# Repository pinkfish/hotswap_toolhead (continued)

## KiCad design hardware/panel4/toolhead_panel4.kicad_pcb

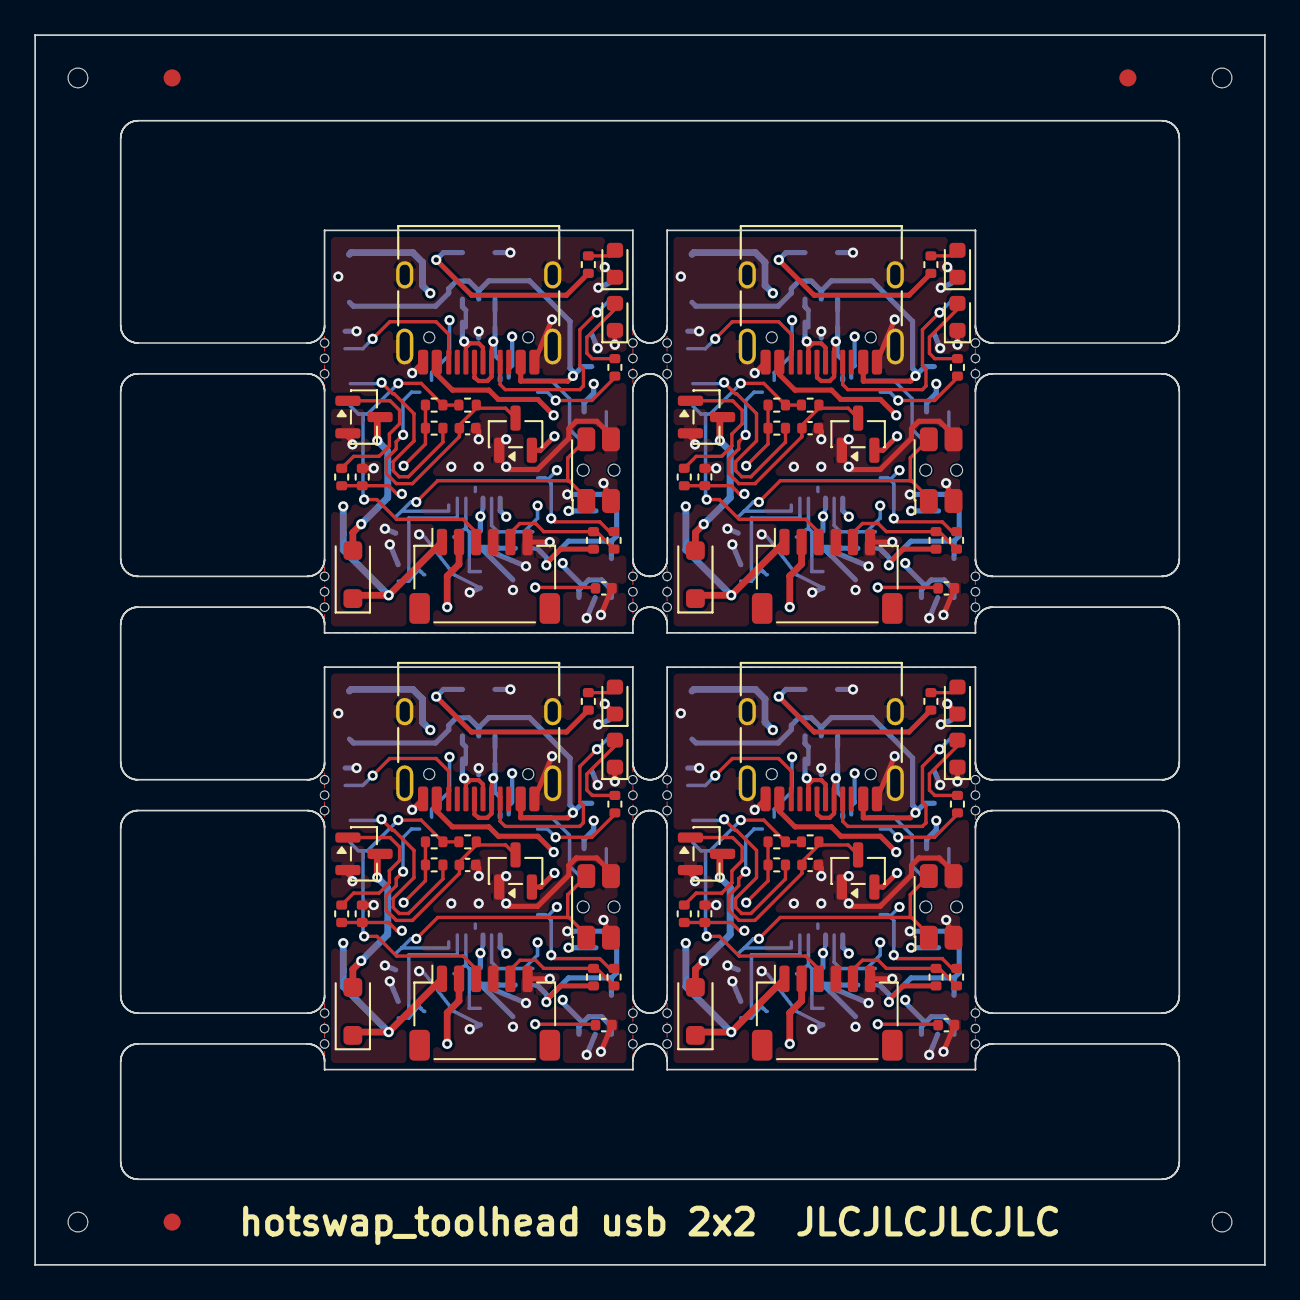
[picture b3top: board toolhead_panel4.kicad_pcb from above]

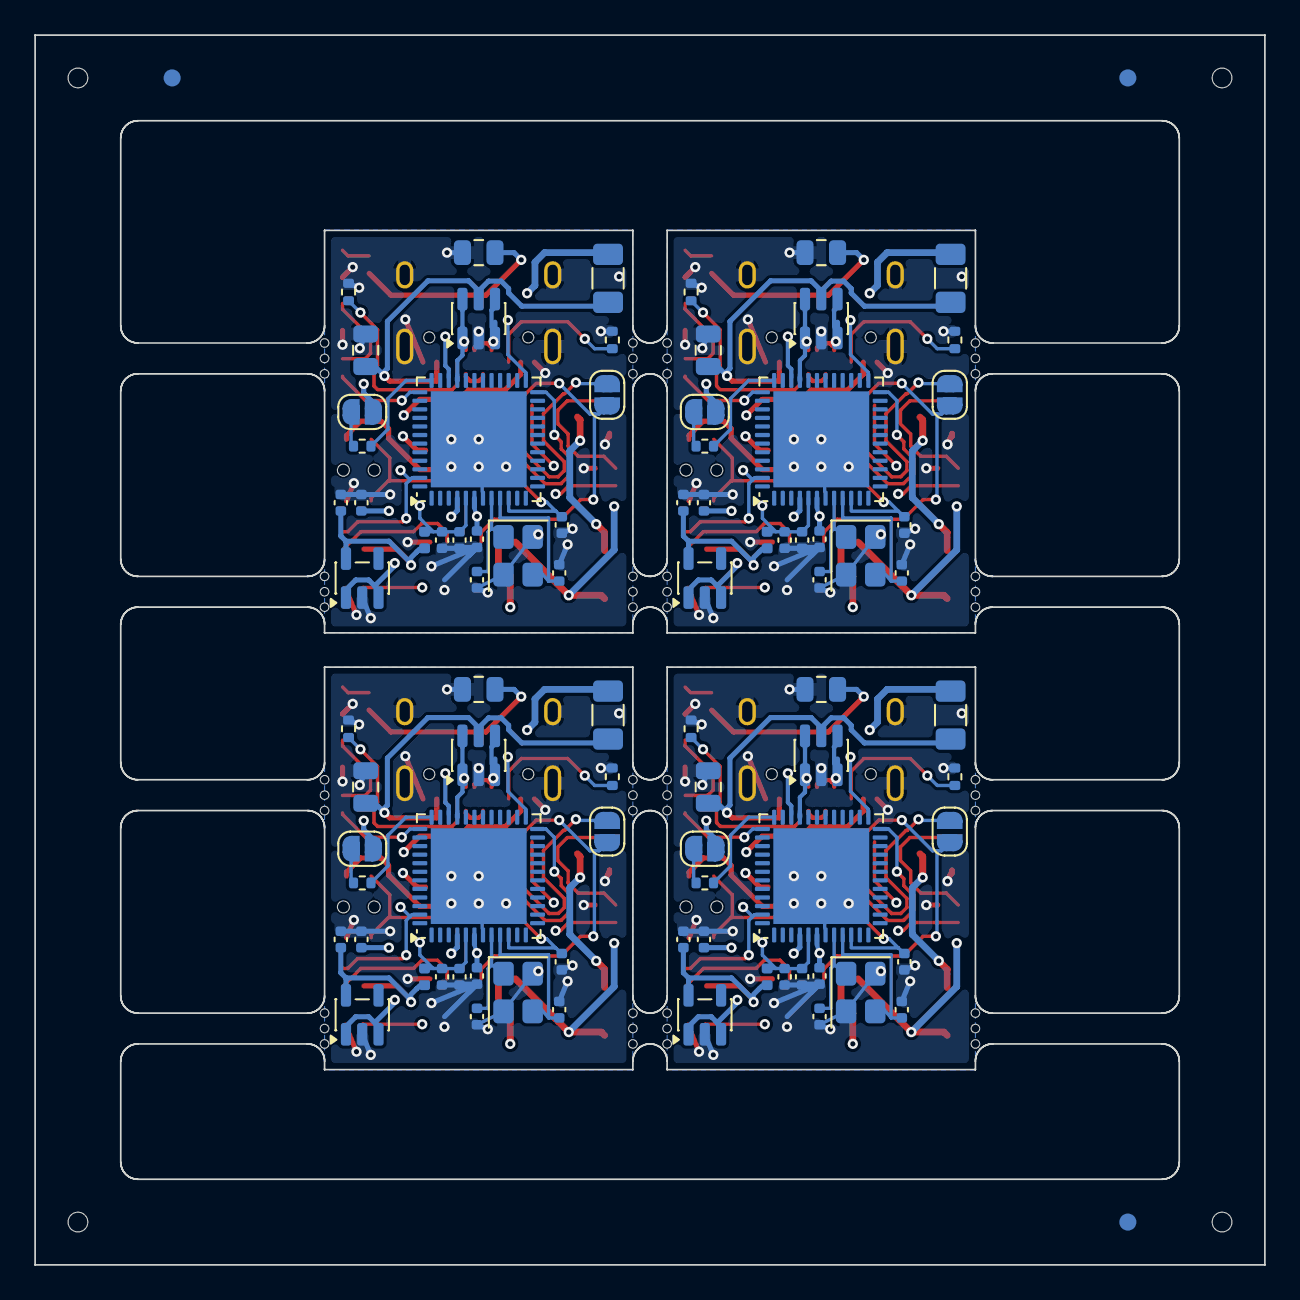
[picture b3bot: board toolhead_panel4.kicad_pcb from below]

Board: 4 copper layers, 71.8 x 71.8 mm, 218 parts (87 on the bottom side), 100 nets.

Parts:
C4_0, C4_1, C4_2, C4_3, C8_0, C8_1, C8_2, C8_3, C11_0, C11_1, C11_2, C11_3: 1uF; C_0402_1005Metric
C9_0, C9_1, C9_2, C9_3, C12_0, C12_1, C12_2, C12_3, C15_0, C15_1, C15_2, C15_3, C19_0, C19_1, C19_2, C19_3, C20_0, C20_1, C20_2, C20_3: 100nF; C_0402_1005Metric
C10_0, C10_1, C10_2, C10_3, C17_0, C17_1, C17_2, C17_3: 10uF 25V X5R; C_0805_2012Metric
C13_0, C13_1, C13_2, C13_3, C14_0, C14_1, C14_2, C14_3: 33pF C0G; C_0402_1005Metric
D5_0, D5_1, D5_2, D5_3: DSK110 100V 1A; D_SOD-123F
D6_0, D6_1, D6_2, D6_3: BAT54S; SOT-23
F2_0, F2_1, F2_2, F2_3: PTC 0.5A 16V (BSMD1206-050-16V); Fuse_1206_3216Metric
FB1_0, FB1_1, FB1_2, FB1_3: 600R@100MHz; L_0402_1005Metric
J2_0, J2_1, J2_2, J2_3: Fan/therm/sensor (JST SH 1x6 SM06B-SRSS-TB); JST_SH_SM06B-SRSS-TB_1x06-1MP_P1.00mm_Horizontal
J5_0, J5_1, J5_2, J5_3: USB-C (HRO TYPE-C-31-M-12); USB_C_Receptacle_HRO_TYPE-C-31-M-12
JP2_0, JP2_1, JP2_2, JP2_3: NTC/PT1000; SolderJumper-2_P1.3mm_Open_RoundedPad1.0x1.5mm
JP3_0, JP3_1, JP3_2, JP3_3: BOOT; SolderJumper-2_P1.3mm_Open_RoundedPad1.0x1.5mm
KiKit_FID_B_1, KiKit_FID_B_2, KiKit_FID_B_3: Fiducial
KiKit_FID_T_1, KiKit_FID_T_2, KiKit_FID_T_3: Fiducial
KiKit_MB_1_1, KiKit_MB_1_2, KiKit_MB_1_3, KiKit_MB_2_1, KiKit_MB_2_2, KiKit_MB_2_3, KiKit_MB_3_1, KiKit_MB_3_2, KiKit_MB_3_3, KiKit_MB_4_1, KiKit_MB_4_2, KiKit_MB_4_3, KiKit_MB_5_1, KiKit_MB_5_2, KiKit_MB_5_3, KiKit_MB_6_1, KiKit_MB_6_2, KiKit_MB_6_3, KiKit_MB_7_1, KiKit_MB_7_2, KiKit_MB_7_3, KiKit_MB_8_1, KiKit_MB_8_2, KiKit_MB_8_3, KiKit_MB_9_1, KiKit_MB_9_2, KiKit_MB_9_3, KiKit_MB_10_1, KiKit_MB_10_2, KiKit_MB_10_3, KiKit_MB_11_1, KiKit_MB_11_2, KiKit_MB_11_3, KiKit_MB_12_1, KiKit_MB_12_2, KiKit_MB_12_3, KiKit_MB_13_1, KiKit_MB_13_2, KiKit_MB_13_3, KiKit_MB_14_1, KiKit_MB_14_2, KiKit_MB_14_3, KiKit_MB_15_1, KiKit_MB_15_2, KiKit_MB_15_3, KiKit_MB_16_1, KiKit_MB_16_2, KiKit_MB_16_3: NPTH
KiKit_TO_1, KiKit_TO_2, KiKit_TO_3, KiKit_TO_4: NPTH
LED1_0, LED1_1, LED1_2, LED1_3: yellow-green; LED_0603_1608Metric
LED2_0, LED2_1, LED2_2, LED2_3: blue; LED_0603_1608Metric
Q3_0, Q3_1, Q3_2, Q3_3: WST6066A; SOT-23
R4_0, R4_1, R4_2, R4_3, R5_0, R5_1, R5_2, R5_3, R15_0, R15_1, R15_2, R15_3, R19_0, R19_1, R19_2, R19_3, R23_0, R23_1, R23_2, R23_3: 1k; R_0402_1005Metric
R6_0, R6_1, R6_2, R6_3: 100R; R_0402_1005Metric
R16_0, R16_1, R16_2, R16_3, R22_0, R22_1, R22_2, R22_3: 10k; R_0402_1005Metric
R17_0, R17_1, R17_2, R17_3: 4.7k 0.1% 25ppm; R_0402_1005Metric
R18_0, R18_1, R18_2, R18_3: 4.12k 0.1% 25ppm; R_0402_1005Metric
R20_0, R20_1, R20_2, R20_3, R21_0, R21_1, R21_2, R21_3: 5.1k; R_0402_1005Metric
SW1_0, SW1_1, SW1_2, SW1_3: RESET; SW_SPST_EVQP7C
U1_0, U1_1, U1_2, U1_3: ME6211C33M5G-N; SOT-23-5
U5_0, U5_1, U5_2, U5_3: USBLC6-2SC6; SOT-23-6
U6_0, U6_1, U6_2, U6_3: STM32G0B1CEU6; QFN-48-1EP_7x7mm_P0.5mm_EP5.6x5.6mm
Y1_0, Y1_1, Y1_2, Y1_3: 8MHz 20pF 3225; Crystal_SMD_3225-4Pin_3.2x2.5mm

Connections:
Board_0-/+3V3: C8_0.1, C9_0.1, C10_0.1, D6_0.2 (K2), FB1_0.1, JP3_0.1, R5_0.1, R22_0.1, U1_0.5, U6_0.4, U6_0.6
Board_0-/BOOT_SW: JP3_0.2, R4_0.1
Board_0-/FAN_G: Q3_0.1, R15_0.2
Board_0-/FAN_N: D5_0.2, J2_0.2, Q3_0.3
Board_0-/FAN_P: D5_0.1, F2_0.2, J2_0.1
Board_0-/FAN_PWM: R15_0.1, R16_0.1, U6_0.25
Board_0-/GND: C4_0.2, C8_0.2, C9_0.2, C10_0.2, C11_0.2, C12_0.2, C13_0.2, C14_0.2, C15_0.2, C17_0.2, C19_0.2, C20_0.2, D6_0.1 (A1), J2_0.4, J2_0.6, J5_0.A1, J5_0.A12, J5_0.B1, J5_0.B12, J5_0.SH, LED1_0.1 (K), LED2_0.1 (K), Q3_0.2, R16_0.2, R20_0.2, R21_0.2, SW1_0.2, U1_0.2, U5_0.2 (GND), U6_0.7, U6_0.49, Y1_0.2, Y1_0.4
Board_0-/JP2_A: JP2_0.2, R18_0.2
Board_0-/LED1_A: LED1_0.2 (A), R5_0.2
Board_0-/LED2_A: LED2_0.2 (A), R6_0.2
Board_0-/LED_STAT: R6_0.1, U6_0.37
Board_0-/NRST: C15_0.1, SW1_0.1, U6_0.10
Board_0-/OSC_IN: C13_0.1, U6_0.8, Y1_0.1
Board_0-/OSC_OUT: C14_0.1, U6_0.9, Y1_0.3
Board_0-/SENS: J2_0.5, R22_0.2, R23_0.1
Board_0-/SENS_IN: C20_0.1, R23_0.2, U6_0.47
Board_0-/SWCLK: R4_0.2, U6_0.36
Board_0-/TH_ADC: C19_0.1, D6_0.3 (K1/A2), R19_0.2, U6_0.24
Board_0-/TH_SIG: J2_0.3, JP2_0.1, R17_0.2, R19_0.1
Board_0-/USB_CC1: J5_0.A5, R20_0.1
Board_0-/USB_CC2: J5_0.B5, R21_0.1
Board_0-/USB_D_N: J5_0.A7, J5_0.B7, U5_0.1 (IO1), U5_0.6 (IO1), U6_0.33
Board_0-/USB_D_P: J5_0.A6, J5_0.B6, U5_0.3 (IO2), U5_0.4 (IO2), U6_0.34
Board_0-/VBUS: C4_0.1, C17_0.1, F2_0.1, J5_0.A4, J5_0.A9, J5_0.B4, J5_0.B9, U1_0.1, U1_0.3, U5_0.5 (VBUS)
Board_0-/VREFP: C11_0.1, C12_0.1, FB1_0.2, R17_0.1, R18_0.1, U6_0.5
Board_1-/+3V3: C8_1.1, C9_1.1, C10_1.1, D6_1.2 (K2), FB1_1.1, JP3_1.1, R5_1.1, R22_1.1, U1_1.5, U6_1.4, U6_1.6
Board_1-/BOOT_SW: JP3_1.2, R4_1.1
Board_1-/FAN_G: Q3_1.1, R15_1.2
Board_1-/FAN_N: D5_1.2, J2_1.2, Q3_1.3
Board_1-/FAN_P: D5_1.1, F2_1.2, J2_1.1
Board_1-/FAN_PWM: R15_1.1, R16_1.1, U6_1.25
Board_1-/GND: C4_1.2, C8_1.2, C9_1.2, C10_1.2, C11_1.2, C12_1.2, C13_1.2, C14_1.2, C15_1.2, C17_1.2, C19_1.2, C20_1.2, D6_1.1 (A1), J2_1.4, J2_1.6, J5_1.A1, J5_1.A12, J5_1.B1, J5_1.B12, J5_1.SH, LED1_1.1 (K), LED2_1.1 (K), Q3_1.2, R16_1.2, R20_1.2, R21_1.2, SW1_1.2, U1_1.2, U5_1.2 (GND), U6_1.7, U6_1.49, Y1_1.2, Y1_1.4
Board_1-/JP2_A: JP2_1.2, R18_1.2
Board_1-/LED1_A: LED1_1.2 (A), R5_1.2
Board_1-/LED2_A: LED2_1.2 (A), R6_1.2
Board_1-/LED_STAT: R6_1.1, U6_1.37
Board_1-/NRST: C15_1.1, SW1_1.1, U6_1.10
Board_1-/OSC_IN: C13_1.1, U6_1.8, Y1_1.1
Board_1-/OSC_OUT: C14_1.1, U6_1.9, Y1_1.3
Board_1-/SENS: J2_1.5, R22_1.2, R23_1.1
Board_1-/SENS_IN: C20_1.1, R23_1.2, U6_1.47
Board_1-/SWCLK: R4_1.2, U6_1.36
Board_1-/TH_ADC: C19_1.1, D6_1.3 (K1/A2), R19_1.2, U6_1.24
Board_1-/TH_SIG: J2_1.3, JP2_1.1, R17_1.2, R19_1.1
Board_1-/USB_CC1: J5_1.A5, R20_1.1
Board_1-/USB_CC2: J5_1.B5, R21_1.1
Board_1-/USB_D_N: J5_1.A7, J5_1.B7, U5_1.1 (IO1), U5_1.6 (IO1), U6_1.33
Board_1-/USB_D_P: J5_1.A6, J5_1.B6, U5_1.3 (IO2), U5_1.4 (IO2), U6_1.34
Board_1-/VBUS: C4_1.1, C17_1.1, F2_1.1, J5_1.A4, J5_1.A9, J5_1.B4, J5_1.B9, U1_1.1, U1_1.3, U5_1.5 (VBUS)
Board_1-/VREFP: C11_1.1, C12_1.1, FB1_1.2, R17_1.1, R18_1.1, U6_1.5
Board_2-/+3V3: C8_2.1, C9_2.1, C10_2.1, D6_2.2 (K2), FB1_2.1, JP3_2.1, R5_2.1, R22_2.1, U1_2.5, U6_2.4, U6_2.6
Board_2-/BOOT_SW: JP3_2.2, R4_2.1
Board_2-/FAN_G: Q3_2.1, R15_2.2
Board_2-/FAN_N: D5_2.2, J2_2.2, Q3_2.3
Board_2-/FAN_P: D5_2.1, F2_2.2, J2_2.1
Board_2-/FAN_PWM: R15_2.1, R16_2.1, U6_2.25
Board_2-/GND: C4_2.2, C8_2.2, C9_2.2, C10_2.2, C11_2.2, C12_2.2, C13_2.2, C14_2.2, C15_2.2, C17_2.2, C19_2.2, C20_2.2, D6_2.1 (A1), J2_2.4, J2_2.6, J5_2.A1, J5_2.A12, J5_2.B1, J5_2.B12, J5_2.SH, LED1_2.1 (K), LED2_2.1 (K), Q3_2.2, R16_2.2, R20_2.2, R21_2.2, SW1_2.2, U1_2.2, U5_2.2 (GND), U6_2.7, U6_2.49, Y1_2.2, Y1_2.4
Board_2-/JP2_A: JP2_2.2, R18_2.2
Board_2-/LED1_A: LED1_2.2 (A), R5_2.2
Board_2-/LED2_A: LED2_2.2 (A), R6_2.2
Board_2-/LED_STAT: R6_2.1, U6_2.37
Board_2-/NRST: C15_2.1, SW1_2.1, U6_2.10
Board_2-/OSC_IN: C13_2.1, U6_2.8, Y1_2.1
Board_2-/OSC_OUT: C14_2.1, U6_2.9, Y1_2.3
Board_2-/SENS: J2_2.5, R22_2.2, R23_2.1
Board_2-/SENS_IN: C20_2.1, R23_2.2, U6_2.47
Board_2-/SWCLK: R4_2.2, U6_2.36
Board_2-/TH_ADC: C19_2.1, D6_2.3 (K1/A2), R19_2.2, U6_2.24
Board_2-/TH_SIG: J2_2.3, JP2_2.1, R17_2.2, R19_2.1
Board_2-/USB_CC1: J5_2.A5, R20_2.1
Board_2-/USB_CC2: J5_2.B5, R21_2.1
Board_2-/USB_D_N: J5_2.A7, J5_2.B7, U5_2.1 (IO1), U5_2.6 (IO1), U6_2.33
Board_2-/USB_D_P: J5_2.A6, J5_2.B6, U5_2.3 (IO2), U5_2.4 (IO2), U6_2.34
Board_2-/VBUS: C4_2.1, C17_2.1, F2_2.1, J5_2.A4, J5_2.A9, J5_2.B4, J5_2.B9, U1_2.1, U1_2.3, U5_2.5 (VBUS)
Board_2-/VREFP: C11_2.1, C12_2.1, FB1_2.2, R17_2.1, R18_2.1, U6_2.5
Board_3-/+3V3: C8_3.1, C9_3.1, C10_3.1, D6_3.2 (K2), FB1_3.1, JP3_3.1, R5_3.1, R22_3.1, U1_3.5, U6_3.4, U6_3.6
Board_3-/BOOT_SW: JP3_3.2, R4_3.1
Board_3-/FAN_G: Q3_3.1, R15_3.2
Board_3-/FAN_N: D5_3.2, J2_3.2, Q3_3.3
Board_3-/FAN_P: D5_3.1, F2_3.2, J2_3.1
Board_3-/FAN_PWM: R15_3.1, R16_3.1, U6_3.25
Board_3-/GND: C4_3.2, C8_3.2, C9_3.2, C10_3.2, C11_3.2, C12_3.2, C13_3.2, C14_3.2, C15_3.2, C17_3.2, C19_3.2, C20_3.2, D6_3.1 (A1), J2_3.4, J2_3.6, J5_3.A1, J5_3.A12, J5_3.B1, J5_3.B12, J5_3.SH, LED1_3.1 (K), LED2_3.1 (K), Q3_3.2, R16_3.2, R20_3.2, R21_3.2, SW1_3.2, U1_3.2, U5_3.2 (GND), U6_3.7, U6_3.49, Y1_3.2, Y1_3.4
Board_3-/JP2_A: JP2_3.2, R18_3.2
Board_3-/LED1_A: LED1_3.2 (A), R5_3.2
Board_3-/LED2_A: LED2_3.2 (A), R6_3.2
Board_3-/LED_STAT: R6_3.1, U6_3.37
Board_3-/NRST: C15_3.1, SW1_3.1, U6_3.10
Board_3-/OSC_IN: C13_3.1, U6_3.8, Y1_3.1
Board_3-/OSC_OUT: C14_3.1, U6_3.9, Y1_3.3
Board_3-/SENS: J2_3.5, R22_3.2, R23_3.1
Board_3-/SENS_IN: C20_3.1, R23_3.2, U6_3.47
Board_3-/SWCLK: R4_3.2, U6_3.36
Board_3-/TH_ADC: C19_3.1, D6_3.3 (K1/A2), R19_3.2, U6_3.24
Board_3-/TH_SIG: J2_3.3, JP2_3.1, R17_3.2, R19_3.1
Board_3-/USB_CC1: J5_3.A5, R20_3.1
Board_3-/USB_CC2: J5_3.B5, R21_3.1
Board_3-/USB_D_N: J5_3.A7, J5_3.B7, U5_3.1 (IO1), U5_3.6 (IO1), U6_3.33
Board_3-/USB_D_P: J5_3.A6, J5_3.B6, U5_3.3 (IO2), U5_3.4 (IO2), U6_3.34
Board_3-/VBUS: C4_3.1, C17_3.1, F2_3.1, J5_3.A4, J5_3.A9, J5_3.B4, J5_3.B9, U1_3.1, U1_3.3, U5_3.5 (VBUS)
Board_3-/VREFP: C11_3.1, C12_3.1, FB1_3.2, R17_3.1, R18_3.1, U6_3.5

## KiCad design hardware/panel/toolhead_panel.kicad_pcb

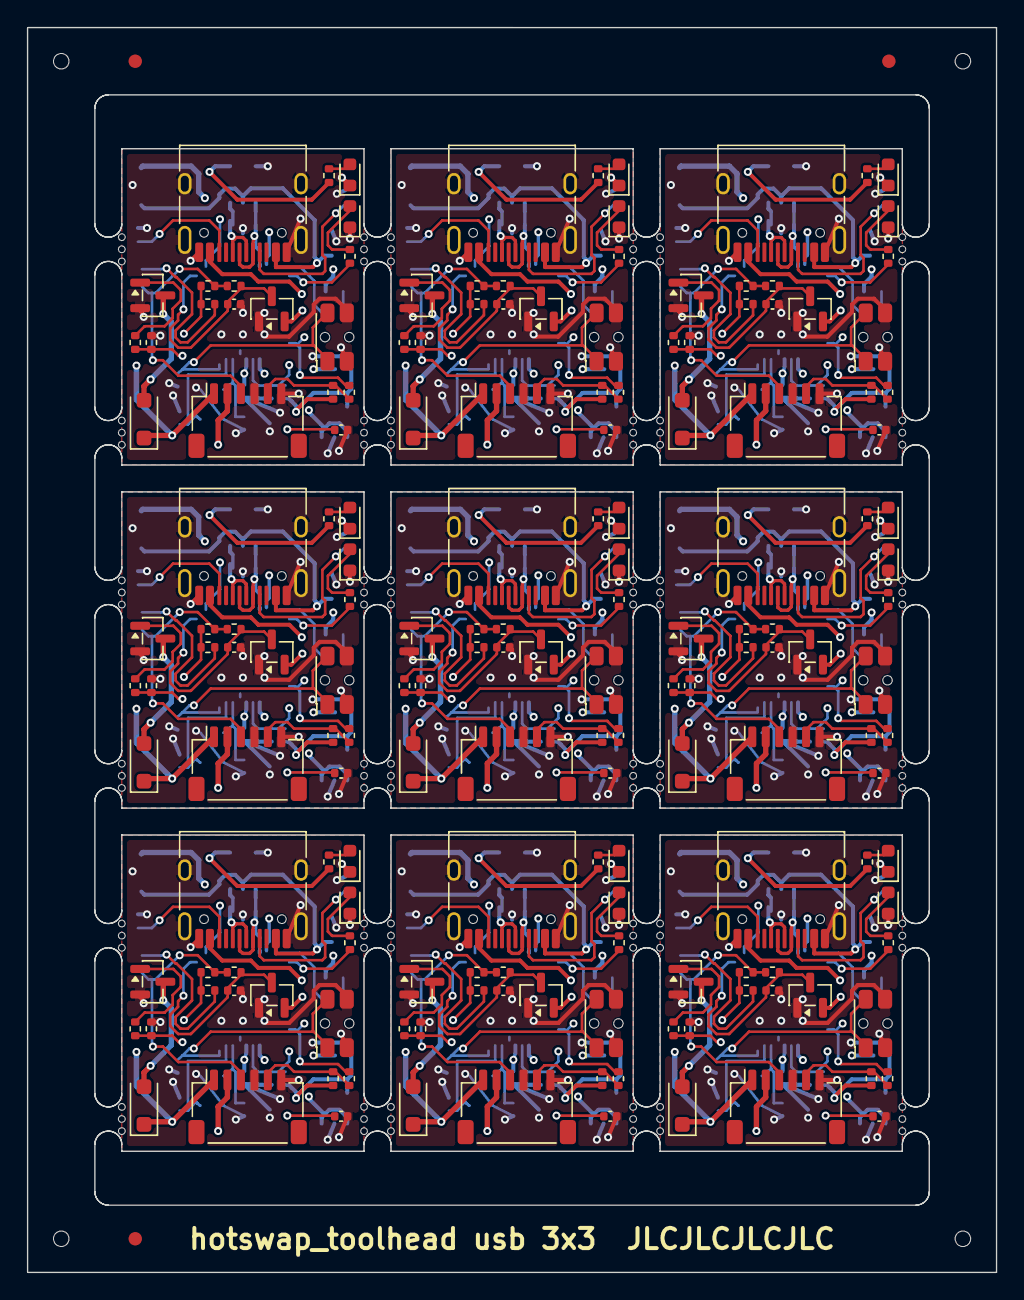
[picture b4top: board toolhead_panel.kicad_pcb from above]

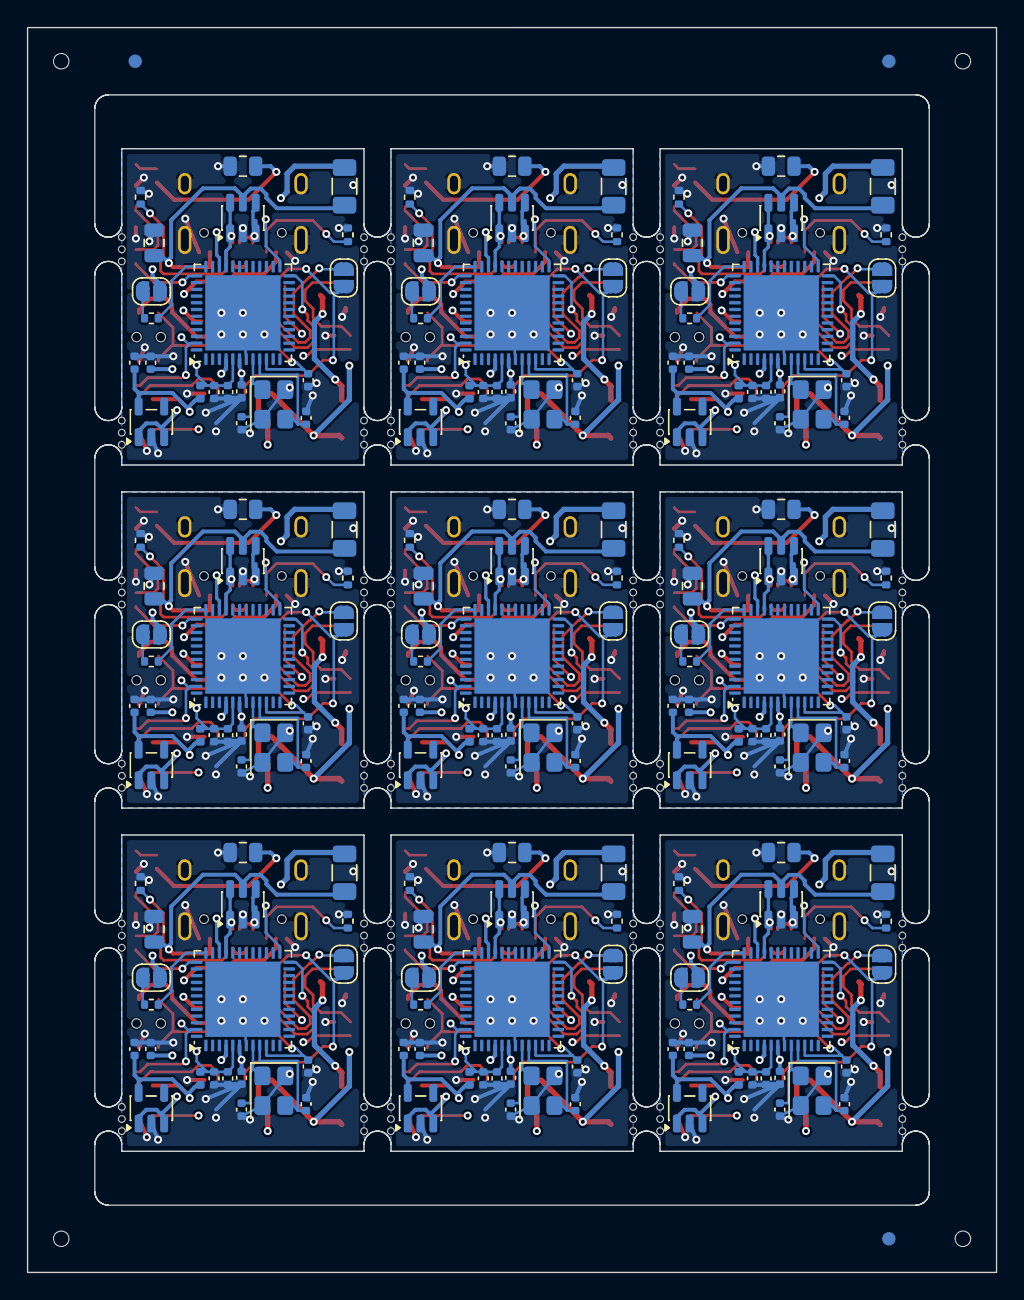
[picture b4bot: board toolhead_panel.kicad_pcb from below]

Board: 4 copper layers, 72.0 x 92.5 mm, 478 parts (192 on the bottom side), 225 nets.

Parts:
C4_0, C4_1, C4_2, C4_3, C4_4, C4_5, C4_6, C4_7, C4_8, C8_0, C8_1, C8_2, C8_3, C8_4, C8_5, C8_6, C8_7, C8_8, C11_0, C11_1, C11_2, C11_3, C11_4, C11_5, C11_6, C11_7, C11_8: 1uF; C_0402_1005Metric
C9_0, C9_1, C9_2, C9_3, C9_4, C9_5, C9_6, C9_7, C9_8, C12_0, C12_1, C12_2, C12_3, C12_4, C12_5, C12_6, C12_7, C12_8, C15_0, C15_1, C15_2, C15_3, C15_4, C15_5, C15_6, C15_7, C15_8, C19_0, C19_1, C19_2, C19_3, C19_4, C19_5, C19_6, C19_7, C19_8, C20_0, C20_1, C20_2, C20_3, C20_4, C20_5, C20_6, C20_7, C20_8: 100nF; C_0402_1005Metric
C10_0, C10_1, C10_2, C10_3, C10_4, C10_5, C10_6, C10_7, C10_8, C17_0, C17_1, C17_2, C17_3, C17_4, C17_5, C17_6, C17_7, C17_8: 10uF 25V X5R; C_0805_2012Metric
C13_0, C13_1, C13_2, C13_3, C13_4, C13_5, C13_6, C13_7, C13_8, C14_0, C14_1, C14_2, C14_3, C14_4, C14_5, C14_6, C14_7, C14_8: 33pF C0G; C_0402_1005Metric
D5_0, D5_1, D5_2, D5_3, D5_4, D5_5, D5_6, D5_7, D5_8: DSK110 100V 1A; D_SOD-123F
D6_0, D6_1, D6_2, D6_3, D6_4, D6_5, D6_6, D6_7, D6_8: BAT54S; SOT-23
F2_0, F2_1, F2_2, F2_3, F2_4, F2_5, F2_6, F2_7, F2_8: PTC 0.5A 16V (BSMD1206-050-16V); Fuse_1206_3216Metric
FB1_0, FB1_1, FB1_2, FB1_3, FB1_4, FB1_5, FB1_6, FB1_7, FB1_8: 600R@100MHz; L_0402_1005Metric
J2_0, J2_1, J2_2, J2_3, J2_4, J2_5, J2_6, J2_7, J2_8: Fan/therm/sensor (JST SH 1x6 SM06B-SRSS-TB); JST_SH_SM06B-SRSS-TB_1x06-1MP_P1.00mm_Horizontal
J5_0, J5_1, J5_2, J5_3, J5_4, J5_5, J5_6, J5_7, J5_8: USB-C (HRO TYPE-C-31-M-12); USB_C_Receptacle_HRO_TYPE-C-31-M-12
JP2_0, JP2_1, JP2_2, JP2_3, JP2_4, JP2_5, JP2_6, JP2_7, JP2_8: NTC/PT1000; SolderJumper-2_P1.3mm_Open_RoundedPad1.0x1.5mm
JP3_0, JP3_1, JP3_2, JP3_3, JP3_4, JP3_5, JP3_6, JP3_7, JP3_8: BOOT; SolderJumper-2_P1.3mm_Open_RoundedPad1.0x1.5mm
KiKit_FID_B_1, KiKit_FID_B_2, KiKit_FID_B_3: Fiducial
KiKit_FID_T_1, KiKit_FID_T_2, KiKit_FID_T_3: Fiducial
KiKit_MB_1_1, KiKit_MB_1_2, KiKit_MB_1_3, KiKit_MB_2_1, KiKit_MB_2_2, KiKit_MB_2_3, KiKit_MB_3_1, KiKit_MB_3_2, KiKit_MB_3_3, KiKit_MB_4_1, KiKit_MB_4_2, KiKit_MB_4_3, KiKit_MB_5_1, KiKit_MB_5_2, KiKit_MB_5_3, KiKit_MB_6_1, KiKit_MB_6_2, KiKit_MB_6_3, KiKit_MB_7_1, KiKit_MB_7_2, KiKit_MB_7_3, KiKit_MB_8_1, KiKit_MB_8_2, KiKit_MB_8_3, KiKit_MB_9_1, KiKit_MB_9_2, KiKit_MB_9_3, KiKit_MB_10_1, KiKit_MB_10_2, KiKit_MB_10_3, KiKit_MB_11_1, KiKit_MB_11_2, KiKit_MB_11_3, KiKit_MB_12_1, KiKit_MB_12_2, KiKit_MB_12_3, KiKit_MB_13_1, KiKit_MB_13_2, KiKit_MB_13_3, KiKit_MB_14_1, KiKit_MB_14_2, KiKit_MB_14_3, KiKit_MB_15_1, KiKit_MB_15_2, KiKit_MB_15_3, KiKit_MB_16_1, KiKit_MB_16_2, KiKit_MB_16_3, KiKit_MB_17_1, KiKit_MB_17_2, KiKit_MB_17_3, KiKit_MB_18_1, KiKit_MB_18_2, KiKit_MB_18_3, KiKit_MB_19_1, KiKit_MB_19_2, KiKit_MB_19_3, KiKit_MB_20_1, KiKit_MB_20_2, KiKit_MB_20_3, KiKit_MB_21_1, KiKit_MB_21_2, KiKit_MB_21_3, KiKit_MB_22_1, KiKit_MB_22_2, KiKit_MB_22_3, KiKit_MB_23_1, KiKit_MB_23_2, KiKit_MB_23_3, KiKit_MB_24_1, KiKit_MB_24_2, KiKit_MB_24_3, KiKit_MB_25_1, KiKit_MB_25_2, KiKit_MB_25_3, KiKit_MB_26_1, KiKit_MB_26_2, KiKit_MB_26_3, KiKit_MB_27_1, KiKit_MB_27_2, KiKit_MB_27_3, KiKit_MB_28_1, KiKit_MB_28_2, KiKit_MB_28_3, KiKit_MB_29_1, KiKit_MB_29_2, KiKit_MB_29_3, KiKit_MB_30_1, KiKit_MB_30_2, KiKit_MB_30_3, KiKit_MB_31_1, KiKit_MB_31_2, KiKit_MB_31_3, KiKit_MB_32_1, KiKit_MB_32_2, KiKit_MB_32_3, KiKit_MB_33_1, KiKit_MB_33_2, KiKit_MB_33_3, KiKit_MB_34_1, KiKit_MB_34_2, KiKit_MB_34_3, KiKit_MB_35_1, KiKit_MB_35_2, KiKit_MB_35_3, KiKit_MB_36_1, KiKit_MB_36_2, KiKit_MB_36_3: NPTH
KiKit_TO_1, KiKit_TO_2, KiKit_TO_3, KiKit_TO_4: NPTH
LED1_0, LED1_1, LED1_2, LED1_3, LED1_4, LED1_5, LED1_6, LED1_7, LED1_8: yellow-green; LED_0603_1608Metric
LED2_0, LED2_1, LED2_2, LED2_3, LED2_4, LED2_5, LED2_6, LED2_7, LED2_8: blue; LED_0603_1608Metric
Q3_0, Q3_1, Q3_2, Q3_3, Q3_4, Q3_5, Q3_6, Q3_7, Q3_8: WST6066A; SOT-23
R4_0, R4_1, R4_2, R4_3, R4_4, R4_5, R4_6, R4_7, R4_8, R5_0, R5_1, R5_2, R5_3, R5_4, R5_5, R5_6, R5_7, R5_8, R15_0, R15_1, R15_2, R15_3, R15_4, R15_5, R15_6, R15_7, R15_8, R19_0, R19_1, R19_2, R19_3, R19_4, R19_5, R19_6, R19_7, R19_8, R23_0, R23_1, R23_2, R23_3, R23_4, R23_5, R23_6, R23_7, R23_8: 1k; R_0402_1005Metric
R6_0, R6_1, R6_2, R6_3, R6_4, R6_5, R6_6, R6_7, R6_8: 100R; R_0402_1005Metric
R16_0, R16_1, R16_2, R16_3, R16_4, R16_5, R16_6, R16_7, R16_8, R22_0, R22_1, R22_2, R22_3, R22_4, R22_5, R22_6, R22_7, R22_8: 10k; R_0402_1005Metric
R17_0, R17_1, R17_2, R17_3, R17_4, R17_5, R17_6, R17_7, R17_8: 4.7k 0.1% 25ppm; R_0402_1005Metric
R18_0, R18_1, R18_2, R18_3, R18_4, R18_5, R18_6, R18_7, R18_8: 4.12k 0.1% 25ppm; R_0402_1005Metric
R20_0, R20_1, R20_2, R20_3, R20_4, R20_5, R20_6, R20_7, R20_8, R21_0, R21_1, R21_2, R21_3, R21_4, R21_5, R21_6, R21_7, R21_8: 5.1k; R_0402_1005Metric
SW1_0, SW1_1, SW1_2, SW1_3, SW1_4, SW1_5, SW1_6, SW1_7, SW1_8: RESET; SW_SPST_EVQP7C
U1_0, U1_1, U1_2, U1_3, U1_4, U1_5, U1_6, U1_7, U1_8: ME6211C33M5G-N; SOT-23-5
U5_0, U5_1, U5_2, U5_3, U5_4, U5_5, U5_6, U5_7, U5_8: USBLC6-2SC6; SOT-23-6
U6_0, U6_1, U6_2, U6_3, U6_4, U6_5, U6_6, U6_7, U6_8: STM32G0B1CEU6; QFN-48-1EP_7x7mm_P0.5mm_EP5.6x5.6mm
Y1_0, Y1_1, Y1_2, Y1_3, Y1_4, Y1_5, Y1_6, Y1_7, Y1_8: 8MHz 20pF 3225; Crystal_SMD_3225-4Pin_3.2x2.5mm

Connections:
Board_0-/+3V3: C8_0.1, C9_0.1, C10_0.1, D6_0.2 (K2), FB1_0.1, JP3_0.1, R5_0.1, R22_0.1, U1_0.5, U6_0.4, U6_0.6
Board_0-/BOOT_SW: JP3_0.2, R4_0.1
Board_0-/FAN_G: Q3_0.1, R15_0.2
Board_0-/FAN_N: D5_0.2, J2_0.2, Q3_0.3
Board_0-/FAN_P: D5_0.1, F2_0.2, J2_0.1
Board_0-/FAN_PWM: R15_0.1, R16_0.1, U6_0.25
Board_0-/GND: C4_0.2, C8_0.2, C9_0.2, C10_0.2, C11_0.2, C12_0.2, C13_0.2, C14_0.2, C15_0.2, C17_0.2, C19_0.2, C20_0.2, D6_0.1 (A1), J2_0.4, J2_0.6, J5_0.A1, J5_0.A12, J5_0.B1, J5_0.B12, J5_0.SH, LED1_0.1 (K), LED2_0.1 (K), Q3_0.2, R16_0.2, R20_0.2, R21_0.2, SW1_0.2, U1_0.2, U5_0.2 (GND), U6_0.7, U6_0.49, Y1_0.2, Y1_0.4
Board_0-/JP2_A: JP2_0.2, R18_0.2
Board_0-/LED1_A: LED1_0.2 (A), R5_0.2
Board_0-/LED2_A: LED2_0.2 (A), R6_0.2
Board_0-/LED_STAT: R6_0.1, U6_0.37
Board_0-/NRST: C15_0.1, SW1_0.1, U6_0.10
Board_0-/OSC_IN: C13_0.1, U6_0.8, Y1_0.1
Board_0-/OSC_OUT: C14_0.1, U6_0.9, Y1_0.3
Board_0-/SENS: J2_0.5, R22_0.2, R23_0.1
Board_0-/SENS_IN: C20_0.1, R23_0.2, U6_0.47
Board_0-/SWCLK: R4_0.2, U6_0.36
Board_0-/TH_ADC: C19_0.1, D6_0.3 (K1/A2), R19_0.2, U6_0.24
Board_0-/TH_SIG: J2_0.3, JP2_0.1, R17_0.2, R19_0.1
Board_0-/USB_CC1: J5_0.A5, R20_0.1
Board_0-/USB_CC2: J5_0.B5, R21_0.1
Board_0-/USB_D_N: J5_0.A7, J5_0.B7, U5_0.1 (IO1), U5_0.6 (IO1), U6_0.33
Board_0-/USB_D_P: J5_0.A6, J5_0.B6, U5_0.3 (IO2), U5_0.4 (IO2), U6_0.34
Board_0-/VBUS: C4_0.1, C17_0.1, F2_0.1, J5_0.A4, J5_0.A9, J5_0.B4, J5_0.B9, U1_0.1, U1_0.3, U5_0.5 (VBUS)
Board_0-/VREFP: C11_0.1, C12_0.1, FB1_0.2, R17_0.1, R18_0.1, U6_0.5
Board_1-/+3V3: C8_1.1, C9_1.1, C10_1.1, D6_1.2 (K2), FB1_1.1, JP3_1.1, R5_1.1, R22_1.1, U1_1.5, U6_1.4, U6_1.6
Board_1-/BOOT_SW: JP3_1.2, R4_1.1
Board_1-/FAN_G: Q3_1.1, R15_1.2
Board_1-/FAN_N: D5_1.2, J2_1.2, Q3_1.3
Board_1-/FAN_P: D5_1.1, F2_1.2, J2_1.1
Board_1-/FAN_PWM: R15_1.1, R16_1.1, U6_1.25
Board_1-/GND: C4_1.2, C8_1.2, C9_1.2, C10_1.2, C11_1.2, C12_1.2, C13_1.2, C14_1.2, C15_1.2, C17_1.2, C19_1.2, C20_1.2, D6_1.1 (A1), J2_1.4, J2_1.6, J5_1.A1, J5_1.A12, J5_1.B1, J5_1.B12, J5_1.SH, LED1_1.1 (K), LED2_1.1 (K), Q3_1.2, R16_1.2, R20_1.2, R21_1.2, SW1_1.2, U1_1.2, U5_1.2 (GND), U6_1.7, U6_1.49, Y1_1.2, Y1_1.4
Board_1-/JP2_A: JP2_1.2, R18_1.2
Board_1-/LED1_A: LED1_1.2 (A), R5_1.2
Board_1-/LED2_A: LED2_1.2 (A), R6_1.2
Board_1-/LED_STAT: R6_1.1, U6_1.37
Board_1-/NRST: C15_1.1, SW1_1.1, U6_1.10
Board_1-/OSC_IN: C13_1.1, U6_1.8, Y1_1.1
Board_1-/OSC_OUT: C14_1.1, U6_1.9, Y1_1.3
Board_1-/SENS: J2_1.5, R22_1.2, R23_1.1
Board_1-/SENS_IN: C20_1.1, R23_1.2, U6_1.47
Board_1-/SWCLK: R4_1.2, U6_1.36
Board_1-/TH_ADC: C19_1.1, D6_1.3 (K1/A2), R19_1.2, U6_1.24
Board_1-/TH_SIG: J2_1.3, JP2_1.1, R17_1.2, R19_1.1
Board_1-/USB_CC1: J5_1.A5, R20_1.1
Board_1-/USB_CC2: J5_1.B5, R21_1.1
Board_1-/USB_D_N: J5_1.A7, J5_1.B7, U5_1.1 (IO1), U5_1.6 (IO1), U6_1.33
Board_1-/USB_D_P: J5_1.A6, J5_1.B6, U5_1.3 (IO2), U5_1.4 (IO2), U6_1.34
Board_1-/VBUS: C4_1.1, C17_1.1, F2_1.1, J5_1.A4, J5_1.A9, J5_1.B4, J5_1.B9, U1_1.1, U1_1.3, U5_1.5 (VBUS)
Board_1-/VREFP: C11_1.1, C12_1.1, FB1_1.2, R17_1.1, R18_1.1, U6_1.5
Board_2-/+3V3: C8_2.1, C9_2.1, C10_2.1, D6_2.2 (K2), FB1_2.1, JP3_2.1, R5_2.1, R22_2.1, U1_2.5, U6_2.4, U6_2.6
Board_2-/BOOT_SW: JP3_2.2, R4_2.1
Board_2-/FAN_G: Q3_2.1, R15_2.2
Board_2-/FAN_N: D5_2.2, J2_2.2, Q3_2.3
Board_2-/FAN_P: D5_2.1, F2_2.2, J2_2.1
Board_2-/FAN_PWM: R15_2.1, R16_2.1, U6_2.25
Board_2-/GND: C4_2.2, C8_2.2, C9_2.2, C10_2.2, C11_2.2, C12_2.2, C13_2.2, C14_2.2, C15_2.2, C17_2.2, C19_2.2, C20_2.2, D6_2.1 (A1), J2_2.4, J2_2.6, J5_2.A1, J5_2.A12, J5_2.B1, J5_2.B12, J5_2.SH, LED1_2.1 (K), LED2_2.1 (K), Q3_2.2, R16_2.2, R20_2.2, R21_2.2, SW1_2.2, U1_2.2, U5_2.2 (GND), U6_2.7, U6_2.49, Y1_2.2, Y1_2.4
Board_2-/JP2_A: JP2_2.2, R18_2.2
Board_2-/LED1_A: LED1_2.2 (A), R5_2.2
Board_2-/LED2_A: LED2_2.2 (A), R6_2.2
Board_2-/LED_STAT: R6_2.1, U6_2.37
Board_2-/NRST: C15_2.1, SW1_2.1, U6_2.10
Board_2-/OSC_IN: C13_2.1, U6_2.8, Y1_2.1
Board_2-/OSC_OUT: C14_2.1, U6_2.9, Y1_2.3
Board_2-/SENS: J2_2.5, R22_2.2, R23_2.1
Board_2-/SENS_IN: C20_2.1, R23_2.2, U6_2.47
Board_2-/SWCLK: R4_2.2, U6_2.36
Board_2-/TH_ADC: C19_2.1, D6_2.3 (K1/A2), R19_2.2, U6_2.24
Board_2-/TH_SIG: J2_2.3, JP2_2.1, R17_2.2, R19_2.1
Board_2-/USB_CC1: J5_2.A5, R20_2.1
Board_2-/USB_CC2: J5_2.B5, R21_2.1
Board_2-/USB_D_N: J5_2.A7, J5_2.B7, U5_2.1 (IO1), U5_2.6 (IO1), U6_2.33
Board_2-/USB_D_P: J5_2.A6, J5_2.B6, U5_2.3 (IO2), U5_2.4 (IO2), U6_2.34
Board_2-/VBUS: C4_2.1, C17_2.1, F2_2.1, J5_2.A4, J5_2.A9, J5_2.B4, J5_2.B9, U1_2.1, U1_2.3, U5_2.5 (VBUS)
Board_2-/VREFP: C11_2.1, C12_2.1, FB1_2.2, R17_2.1, R18_2.1, U6_2.5
Board_3-/+3V3: C8_3.1, C9_3.1, C10_3.1, D6_3.2 (K2), FB1_3.1, JP3_3.1, R5_3.1, R22_3.1, U1_3.5, U6_3.4, U6_3.6
Board_3-/BOOT_SW: JP3_3.2, R4_3.1
Board_3-/FAN_G: Q3_3.1, R15_3.2
Board_3-/FAN_N: D5_3.2, J2_3.2, Q3_3.3
Board_3-/FAN_P: D5_3.1, F2_3.2, J2_3.1
Board_3-/FAN_PWM: R15_3.1, R16_3.1, U6_3.25
Board_3-/GND: C4_3.2, C8_3.2, C9_3.2, C10_3.2, C11_3.2, C12_3.2, C13_3.2, C14_3.2, C15_3.2, C17_3.2, C19_3.2, C20_3.2, D6_3.1 (A1), J2_3.4, J2_3.6, J5_3.A1, J5_3.A12, J5_3.B1, J5_3.B12, J5_3.SH, LED1_3.1 (K), LED2_3.1 (K), Q3_3.2, R16_3.2, R20_3.2, R21_3.2, SW1_3.2, U1_3.2, U5_3.2 (GND), U6_3.7, U6_3.49, Y1_3.2, Y1_3.4
Board_3-/JP2_A: JP2_3.2, R18_3.2
Board_3-/LED1_A: LED1_3.2 (A), R5_3.2
Board_3-/LED2_A: LED2_3.2 (A), R6_3.2
Board_3-/LED_STAT: R6_3.1, U6_3.37
Board_3-/NRST: C15_3.1, SW1_3.1, U6_3.10
Board_3-/OSC_IN: C13_3.1, U6_3.8, Y1_3.1
Board_3-/OSC_OUT: C14_3.1, U6_3.9, Y1_3.3
Board_3-/SENS: J2_3.5, R22_3.2, R23_3.1
Board_3-/SENS_IN: C20_3.1, R23_3.2, U6_3.47
Board_3-/SWCLK: R4_3.2, U6_3.36
Board_3-/TH_ADC: C19_3.1, D6_3.3 (K1/A2), R19_3.2, U6_3.24
Board_3-/TH_SIG: J2_3.3, JP2_3.1, R17_3.2, R19_3.1
Board_3-/USB_CC1: J5_3.A5, R20_3.1
Board_3-/USB_CC2: J5_3.B5, R21_3.1
Board_3-/USB_D_N: J5_3.A7, J5_3.B7, U5_3.1 (IO1), U5_3.6 (IO1), U6_3.33
Board_3-/USB_D_P: J5_3.A6, J5_3.B6, U5_3.3 (IO2), U5_3.4 (IO2), U6_3.34
Board_3-/VBUS: C4_3.1, C17_3.1, F2_3.1, J5_3.A4, J5_3.A9, J5_3.B4, J5_3.B9, U1_3.1, U1_3.3, U5_3.5 (VBUS)
Board_3-/VREFP: C11_3.1, C12_3.1, FB1_3.2, R17_3.1, R18_3.1, U6_3.5
Board_4-/+3V3: C8_4.1, C9_4.1, C10_4.1, D6_4.2 (K2), FB1_4.1, JP3_4.1, R5_4.1, R22_4.1, U1_4.5, U6_4.4, U6_4.6
Board_4-/BOOT_SW: JP3_4.2, R4_4.1
Board_4-/FAN_G: Q3_4.1, R15_4.2
Board_4-/FAN_N: D5_4.2, J2_4.2, Q3_4.3
Board_4-/FAN_P: D5_4.1, F2_4.2, J2_4.1
Board_4-/FAN_PWM: R15_4.1, R16_4.1, U6_4.25
Board_4-/GND: C4_4.2, C8_4.2, C9_4.2, C10_4.2, C11_4.2, C12_4.2, C13_4.2, C14_4.2, C15_4.2, C17_4.2, C19_4.2, C20_4.2, D6_4.1 (A1), J2_4.4, J2_4.6, J5_4.A1, J5_4.A12, J5_4.B1, J5_4.B12, J5_4.SH, LED1_4.1 (K), LED2_4.1 (K), Q3_4.2, R16_4.2, R20_4.2, R21_4.2, SW1_4.2, U1_4.2, U5_4.2 (GND), U6_4.7, U6_4.49, Y1_4.2, Y1_4.4
Board_4-/JP2_A: JP2_4.2, R18_4.2
Board_4-/LED1_A: LED1_4.2 (A), R5_4.2
Board_4-/LED2_A: LED2_4.2 (A), R6_4.2
Board_4-/LED_STAT: R6_4.1, U6_4.37
Board_4-/NRST: C15_4.1, SW1_4.1, U6_4.10
Board_4-/OSC_IN: C13_4.1, U6_4.8, Y1_4.1
Board_4-/OSC_OUT: C14_4.1, U6_4.9, Y1_4.3
Board_4-/SENS: J2_4.5, R22_4.2, R23_4.1
Board_4-/SENS_IN: C20_4.1, R23_4.2, U6_4.47
Board_4-/SWCLK: R4_4.2, U6_4.36
Board_4-/TH_ADC: C19_4.1, D6_4.3 (K1/A2), R19_4.2, U6_4.24
Board_4-/TH_SIG: J2_4.3, JP2_4.1, R17_4.2, R19_4.1
Board_4-/USB_CC1: J5_4.A5, R20_4.1
Board_4-/USB_CC2: J5_4.B5, R21_4.1
Board_4-/USB_D_N: J5_4.A7, J5_4.B7, U5_4.1 (IO1), U5_4.6 (IO1), U6_4.33
Board_4-/USB_D_P: J5_4.A6, J5_4.B6, U5_4.3 (IO2), U5_4.4 (IO2), U6_4.34
Board_4-/VBUS: C4_4.1, C17_4.1, F2_4.1, J5_4.A4, J5_4.A9, J5_4.B4, J5_4.B9, U1_4.1, U1_4.3, U5_4.5 (VBUS)
Board_4-/VREFP: C11_4.1, C12_4.1, FB1_4.2, R17_4.1, R18_4.1, U6_4.5
Board_5-/+3V3: C8_5.1, C9_5.1, C10_5.1, D6_5.2 (K2), FB1_5.1, JP3_5.1, R5_5.1, R22_5.1, U1_5.5, U6_5.4, U6_5.6
Board_5-/BOOT_SW: JP3_5.2, R4_5.1
Board_5-/FAN_G: Q3_5.1, R15_5.2
Board_5-/FAN_N: D5_5.2, J2_5.2, Q3_5.3
Board_5-/FAN_P: D5_5.1, F2_5.2, J2_5.1
Board_5-/FAN_PWM: R15_5.1, R16_5.1, U6_5.25
Board_5-/GND: C4_5.2, C8_5.2, C9_5.2, C10_5.2, C11_5.2, C12_5.2, C13_5.2, C14_5.2, C15_5.2, C17_5.2, C19_5.2, C20_5.2, D6_5.1 (A1), J2_5.4, J2_5.6, J5_5.A1, J5_5.A12, J5_5.B1, J5_5.B12, J5_5.SH, LED1_5.1 (K), LED2_5.1 (K), Q3_5.2, R16_5.2, R20_5.2, R21_5.2, SW1_5.2, U1_5.2, U5_5.2 (GND), U6_5.7, U6_5.49, Y1_5.2, Y1_5.4
Board_5-/JP2_A: JP2_5.2, R18_5.2
Board_5-/LED1_A: LED1_5.2 (A), R5_5.2
Board_5-/LED2_A: LED2_5.2 (A), R6_5.2
Board_5-/LED_STAT: R6_5.1, U6_5.37
Board_5-/NRST: C15_5.1, SW1_5.1, U6_5.10
Board_5-/OSC_IN: C13_5.1, U6_5.8, Y1_5.1
Board_5-/OSC_OUT: C14_5.1, U6_5.9, Y1_5.3
Board_5-/SENS: J2_5.5, R22_5.2, R23_5.1
Board_5-/SENS_IN: C20_5.1, R23_5.2, U6_5.47
Board_5-/SWCLK: R4_5.2, U6_5.36
Board_5-/TH_ADC: C19_5.1, D6_5.3 (K1/A2), R19_5.2, U6_5.24
Board_5-/TH_SIG: J2_5.3, JP2_5.1, R17_5.2, R19_5.1
Board_5-/USB_CC1: J5_5.A5, R20_5.1
Board_5-/USB_CC2: J5_5.B5, R21_5.1
Board_5-/USB_D_N: J5_5.A7, J5_5.B7, U5_5.1 (IO1), U5_5.6 (IO1), U6_5.33
Board_5-/USB_D_P: J5_5.A6, J5_5.B6, U5_5.3 (IO2), U5_5.4 (IO2), U6_5.34
Board_5-/VBUS: C4_5.1, C17_5.1, F2_5.1, J5_5.A4, J5_5.A9, J5_5.B4, J5_5.B9, U1_5.1, U1_5.3, U5_5.5 (VBUS)
Board_5-/VREFP: C11_5.1, C12_5.1, FB1_5.2, R17_5.1, R18_5.1, U6_5.5
Board_6-/+3V3: C8_6.1, C9_6.1, C10_6.1, D6_6.2 (K2), FB1_6.1, JP3_6.1, R5_6.1, R22_6.1, U1_6.5, U6_6.4, U6_6.6
Board_6-/BOOT_SW: JP3_6.2, R4_6.1
Board_6-/FAN_G: Q3_6.1, R15_6.2
Board_6-/FAN_N: D5_6.2, J2_6.2, Q3_6.3
Board_6-/FAN_P: D5_6.1, F2_6.2, J2_6.1
Board_6-/FAN_PWM: R15_6.1, R16_6.1, U6_6.25
Board_6-/GND: C4_6.2, C8_6.2, C9_6.2, C10_6.2, C11_6.2, C12_6.2, C13_6.2, C14_6.2, C15_6.2, C17_6.2, C19_6.2, C20_6.2, D6_6.1 (A1), J2_6.4, J2_6.6, J5_6.A1, J5_6.A12, J5_6.B1, J5_6.B12, J5_6.SH, LED1_6.1 (K), LED2_6.1 (K), Q3_6.2, R16_6.2, R20_6.2, R21_6.2, SW1_6.2, U1_6.2, U5_6.2 (GND), U6_6.7, U6_6.49, Y1_6.2, Y1_6.4
Board_6-/JP2_A: JP2_6.2, R18_6.2
Board_6-/LED1_A: LED1_6.2 (A), R5_6.2
Board_6-/LED2_A: LED2_6.2 (A), R6_6.2
Board_6-/LED_STAT: R6_6.1, U6_6.37
Board_6-/NRST: C15_6.1, SW1_6.1, U6_6.10
Board_6-/OSC_IN: C13_6.1, U6_6.8, Y1_6.1
Board_6-/OSC_OUT: C14_6.1, U6_6.9, Y1_6.3
Board_6-/SENS: J2_6.5, R22_6.2, R23_6.1
Board_6-/SENS_IN: C20_6.1, R23_6.2, U6_6.47
Board_6-/SWCLK: R4_6.2, U6_6.36
Board_6-/TH_ADC: C19_6.1, D6_6.3 (K1/A2), R19_6.2, U6_6.24
Board_6-/TH_SIG: J2_6.3, JP2_6.1, R17_6.2, R19_6.1
Board_6-/USB_CC1: J5_6.A5, R20_6.1
Board_6-/USB_CC2: J5_6.B5, R21_6.1
Board_6-/USB_D_N: J5_6.A7, J5_6.B7, U5_6.1 (IO1), U5_6.6 (IO1), U6_6.33
Board_6-/USB_D_P: J5_6.A6, J5_6.B6, U5_6.3 (IO2), U5_6.4 (IO2), U6_6.34
Board_6-/VBUS: C4_6.1, C17_6.1, F2_6.1, J5_6.A4, J5_6.A9, J5_6.B4, J5_6.B9, U1_6.1, U1_6.3, U5_6.5 (VBUS)
Board_6-/VREFP: C11_6.1, C12_6.1, FB1_6.2, R17_6.1, R18_6.1, U6_6.5
Board_7-/+3V3: C8_7.1, C9_7.1, C10_7.1, D6_7.2 (K2), FB1_7.1, JP3_7.1, R5_7.1, R22_7.1, U1_7.5, U6_7.4, U6_7.6
Board_7-/BOOT_SW: JP3_7.2, R4_7.1
Board_7-/FAN_G: Q3_7.1, R15_7.2
Board_7-/FAN_N: D5_7.2, J2_7.2, Q3_7.3
Board_7-/FAN_P: D5_7.1, F2_7.2, J2_7.1
Board_7-/FAN_PWM: R15_7.1, R16_7.1, U6_7.25
Board_7-/GND: C4_7.2, C8_7.2, C9_7.2, C10_7.2, C11_7.2, C12_7.2, C13_7.2, C14_7.2, C15_7.2, C17_7.2, C19_7.2, C20_7.2, D6_7.1 (A1), J2_7.4, J2_7.6, J5_7.A1, J5_7.A12, J5_7.B1, J5_7.B12, J5_7.SH, LED1_7.1 (K), LED2_7.1 (K), Q3_7.2, R16_7.2, R20_7.2, R21_7.2, SW1_7.2, U1_7.2, U5_7.2 (GND), U6_7.7, U6_7.49, Y1_7.2, Y1_7.4
Board_7-/JP2_A: JP2_7.2, R18_7.2
Board_7-/LED1_A: LED1_7.2 (A), R5_7.2
Board_7-/LED2_A: LED2_7.2 (A), R6_7.2
Board_7-/LED_STAT: R6_7.1, U6_7.37
Board_7-/NRST: C15_7.1, SW1_7.1, U6_7.10
Board_7-/OSC_IN: C13_7.1, U6_7.8, Y1_7.1
Board_7-/OSC_OUT: C14_7.1, U6_7.9, Y1_7.3
Board_7-/SENS: J2_7.5, R22_7.2, R23_7.1
Board_7-/SENS_IN: C20_7.1, R23_7.2, U6_7.47
Board_7-/SWCLK: R4_7.2, U6_7.36
Board_7-/TH_ADC: C19_7.1, D6_7.3 (K1/A2), R19_7.2, U6_7.24
Board_7-/TH_SIG: J2_7.3, JP2_7.1, R17_7.2, R19_7.1
Board_7-/USB_CC1: J5_7.A5, R20_7.1
Board_7-/USB_CC2: J5_7.B5, R21_7.1
Board_7-/USB_D_N: J5_7.A7, J5_7.B7, U5_7.1 (IO1), U5_7.6 (IO1), U6_7.33
Board_7-/USB_D_P: J5_7.A6, J5_7.B6, U5_7.3 (IO2), U5_7.4 (IO2), U6_7.34
Board_7-/VBUS: C4_7.1, C17_7.1, F2_7.1, J5_7.A4, J5_7.A9, J5_7.B4, J5_7.B9, U1_7.1, U1_7.3, U5_7.5 (VBUS)
Board_7-/VREFP: C11_7.1, C12_7.1, FB1_7.2, R17_7.1, R18_7.1, U6_7.5
Board_8-/+3V3: C8_8.1, C9_8.1, C10_8.1, D6_8.2 (K2), FB1_8.1, JP3_8.1, R5_8.1, R22_8.1, U1_8.5, U6_8.4, U6_8.6
Board_8-/BOOT_SW: JP3_8.2, R4_8.1
Board_8-/FAN_G: Q3_8.1, R15_8.2
Board_8-/FAN_N: D5_8.2, J2_8.2, Q3_8.3
Board_8-/FAN_P: D5_8.1, F2_8.2, J2_8.1
Board_8-/FAN_PWM: R15_8.1, R16_8.1, U6_8.25
Board_8-/GND: C4_8.2, C8_8.2, C9_8.2, C10_8.2, C11_8.2, C12_8.2, C13_8.2, C14_8.2, C15_8.2, C17_8.2, C19_8.2, C20_8.2, D6_8.1 (A1), J2_8.4, J2_8.6, J5_8.A1, J5_8.A12, J5_8.B1, J5_8.B12, J5_8.SH, LED1_8.1 (K), LED2_8.1 (K), Q3_8.2, R16_8.2, R20_8.2, R21_8.2, SW1_8.2, U1_8.2, U5_8.2 (GND), U6_8.7, U6_8.49, Y1_8.2, Y1_8.4
Board_8-/JP2_A: JP2_8.2, R18_8.2
Board_8-/LED1_A: LED1_8.2 (A), R5_8.2
Board_8-/LED2_A: LED2_8.2 (A), R6_8.2
Board_8-/LED_STAT: R6_8.1, U6_8.37
Board_8-/NRST: C15_8.1, SW1_8.1, U6_8.10
Board_8-/OSC_IN: C13_8.1, U6_8.8, Y1_8.1
Board_8-/OSC_OUT: C14_8.1, U6_8.9, Y1_8.3
Board_8-/SENS: J2_8.5, R22_8.2, R23_8.1
Board_8-/SENS_IN: C20_8.1, R23_8.2, U6_8.47
Board_8-/SWCLK: R4_8.2, U6_8.36
Board_8-/TH_ADC: C19_8.1, D6_8.3 (K1/A2), R19_8.2, U6_8.24
Board_8-/TH_SIG: J2_8.3, JP2_8.1, R17_8.2, R19_8.1
Board_8-/USB_CC1: J5_8.A5, R20_8.1
Board_8-/USB_CC2: J5_8.B5, R21_8.1
Board_8-/USB_D_N: J5_8.A7, J5_8.B7, U5_8.1 (IO1), U5_8.6 (IO1), U6_8.33
Board_8-/USB_D_P: J5_8.A6, J5_8.B6, U5_8.3 (IO2), U5_8.4 (IO2), U6_8.34
Board_8-/VBUS: C4_8.1, C17_8.1, F2_8.1, J5_8.A4, J5_8.A9, J5_8.B4, J5_8.B9, U1_8.1, U1_8.3, U5_8.5 (VBUS)
Board_8-/VREFP: C11_8.1, C12_8.1, FB1_8.2, R17_8.1, R18_8.1, U6_8.5
